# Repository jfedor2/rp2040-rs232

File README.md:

# RS-232 adapter with an RP2040 chip

This repository contains design files and firmware for a board that can be used as an RS-232 (serial) to USB adapter. It has an RP2040 chip for the application logic and a MAX3243 chip for the serial interface.

The provided firmware supports classic serial mice, two types of 3D mice (Magellan/SpaceMouse and Spaceball 2003), the SpaceOrb 360 game controller, and can also act as a generic serial-to-USB adapter.

## How to make the device

I used [JLCPCB](https://jlcpcb.com/) to make the board. The files in the [fabrication](fabrication) folder can be used with JLCPCB directly. If you want to use some other service, check the file formats that they expect. When ordering from JLCPCB, upload the Gerber zip, leave all the settings at default (you can choose the PCB color), then enable "PCB Assembly" and upload the BOM and CPL files in the next step.

Models for a 3D-printable case can be found in the [3d-printed-case](3d-printed-case) folder. The cases uses four M2x12 countersunk screws and (optionally) one M2x4 screw to secure the board to the case.

## Firmware

The provided firmware combines five separate projects and lets you choose between them using the DIP switches on the board. This way you can have a multi-purpose adapter without having to re-flash the firmware every time.

To flash the board with the firmware, press and hold the BOOT button, then while holding it press and release the RESET button. A drive named "RPI-RP2" should appear on your computer. Copy the [multi-firmware.uf2](https://github.com/jfedor2/rp2040-rs232/releases/latest/download/multi-firmware.uf2) file to that drive. After it's done flashing the drive will disappear and that's it.

project | description | DIP switch setting
------- | ----------- | ------------------
[HID Remapper](https://github.com/jfedor2/hid-remapper) | Adapts classic serial mice to USB | off-off-off-ON
[spaceball-2003](https://github.com/jfedor2/spaceball-2003) | Lets you use a Spaceball 2003 with modern software | off-off-ON-off
[magellan-spacemouse](https://github.com/jfedor2/magellan-spacemouse) | Lets you use a serial Magellan/SpaceMouse with modern software | off-off-ON-ON
[pico-uart-bridge](https://github.com/Noltari/pico-uart-bridge) | Generic USB-to-serial bridge | off-ON-off-off
[spaceorb360](https://github.com/jfedor2/spaceorb360)<br>(spacemouse) | Lets you use a SpaceOrb 360 with modern CAD software | off-ON-off-ON
[spaceorb360](https://github.com/jfedor2/spaceorb360)<br>(joystick) | Lets you use a SpaceOrb 360 with games like Descent | off-ON-ON-off

You can of course use any other firmware meant for the RP2040 chip if you want.

## How to compile

The easiest way to compile the firmware is to let GitHub do it for you. This repository has GitHub Actions that build the firmware, so you can just fork, enable Actions, make your changes, wait for the job to complete, and look for the binary in the artifacts produced.

To compile the firmware on your machine, use the following steps (details may vary depending on your Linux distribution):

```
sudo apt install gcc-arm-none-eabi libnewlib-arm-none-eabi libstdc++-arm-none-eabi-newlib
git clone https://github.com/jfedor2/rp2040-rs232.git
cd rp2040-rs232/multi-firmware
git submodule update --init
for submodule in hid-remapper magellan-spacemouse spaceball-2003 pico-uart-bridge spaceorb360
do
cd $submodule; git submodule update --init; cd ..
done
mkdir build
cd build
cmake ..
make
```

## License

The software in this repository is licensed under the [MIT License](LICENSE), unless stated otherwise. 

The hardware designs in this repository are licensed under the Creative Commons Attribution 4.0 International license ([CC BY 4.0](https://creativecommons.org/licenses/by/4.0/)), unless stated otherwise.

## Acknowledgments

PCB design uses [Type-C.pretty](https://github.com/ai03-2725/Type-C.pretty) library by [ai03-2725](https://github.com/ai03-2725).

Multi-firmware includes [pico-uart-bridge](https://github.com/Noltari/pico-uart-bridge) by [Noltari](https://github.com/Noltari).

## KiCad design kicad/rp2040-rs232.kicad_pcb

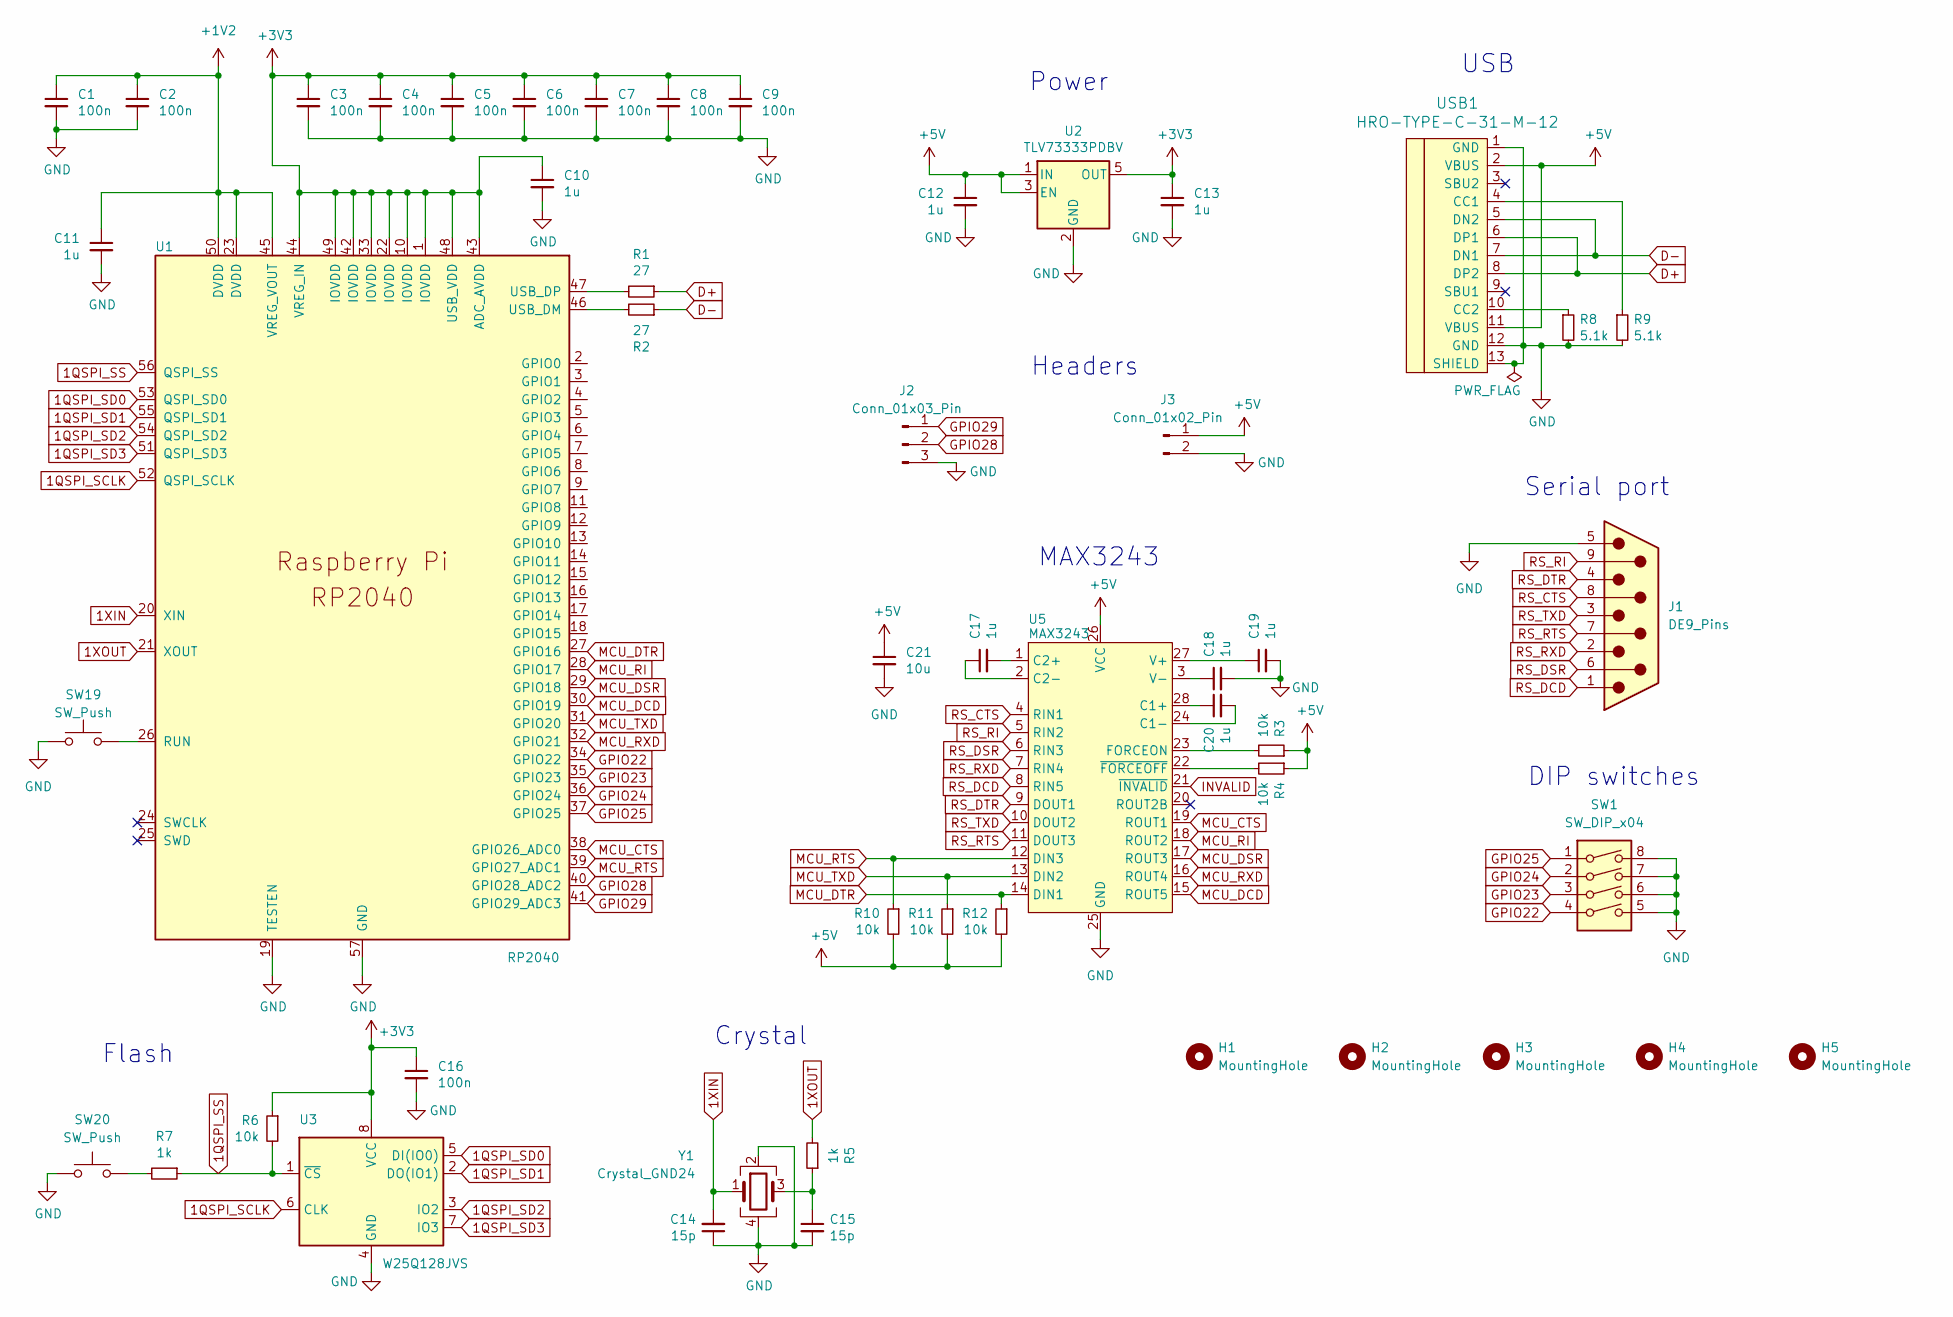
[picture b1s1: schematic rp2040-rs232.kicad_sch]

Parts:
C1, C2, C3, C4, C5, C6, C7, C8, C9, C16: 100n; C_0402_1005Metric; LCSC C1525
C10, C11, C12, C13, C17, C18, C19, C20: 1u; C_0402_1005Metric; LCSC C52923
C14, C15: 15p; C_0402_1005Metric; LCSC C1548
C21: 10u; C_0402_1005Metric; LCSC C15525
H1, H2, H3, H4, H5: MountingHole; MountingHole_2.2mm_M2
J1: DE9_Pins; C19077344; LCSC C19077344
J2: Conn_01x03_Pin; PinHeader_1x03_P2.54mm_Vertical
J3: Conn_01x02_Pin; PinHeader_1x02_P2.54mm_Vertical
R1, R2: 27; R_0402_1005Metric; LCSC C138021
R3, R4, R6, R10, R11, R12: 10k; R_0402_1005Metric; LCSC C25744
R5, R7: 1k; R_0402_1005Metric; LCSC C11702
R8, R9: 5.1k; R_0402_1005Metric; LCSC C25905
SW1: SW_DIP_x04; C92645; LCSC C92645
SW19, SW20: SW_Push; C720477; LCSC C720477
U1: RP2040; RP2040-QFN-56; LCSC C2040
U2: TLV73333PDBV; SOT-23-5; LCSC C134139
U3: W25Q128JVS; SOIC-8_5.23x5.23mm_P1.27mm; LCSC C97521
U5: MAX3243; SSOP-28_5.3x10.2mm_P0.65mm; LCSC C414614
USB1: HRO-TYPE-C-31-M-12; HRO-TYPE-C-31-M-12-Assembly; LCSC C165948
Y1: Crystal_GND24; Crystal_SMD_2520-4Pin_2.5x2.0mm; LCSC C90603

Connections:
1QSPI_SCLK: U1.52 (QSPI_SCLK), U3.6 (CLK)
1QSPI_SD0: U1.53 (QSPI_SD0), U3.5 (DI(IO0))
1QSPI_SD1: U1.55 (QSPI_SD1), U3.2 (DO(IO1))
1QSPI_SD2: U1.54 (QSPI_SD2), U3.3 (IO2)
1QSPI_SD3: U1.51 (QSPI_SD3), U3.7 (IO3)
1QSPI_SS: R6.2, R7.1, U1.56 (QSPI_SS), U3.1 (~CS)
1XIN: C14.2, U1.20 (XIN), Y1.1
1XOUT: R5.2, U1.21 (XOUT)
+1V2: C1.1, C2.1, C11.1, U1.23 (DVDD), U1.45 (VREG_VOUT), U1.50 (DVDD)
+3V3: C3.1, C4.1, C5.1, C6.1, C7.1, C8.1, C9.1, C10.1, C13.1, C16.1, R6.1, U1.1 (IOVDD), U1.10 (IOVDD), U1.22 (IOVDD), U1.33 (IOVDD), U1.42 (IOVDD), U1.43 (ADC_AVDD), U1.44 (VREG_IN), U1.48 (USB_VDD), U1.49 (IOVDD), U2.5 (OUT), U3.8 (VCC)
+5V: C12.1, C21.1, J3.1, R3.1, R4.1, R10.2, R11.2, R12.2, U2.1 (IN), U2.3 (EN), U5.26 (VCC), USB1.2 (VBUS), USB1.11 (VBUS)
D+: R1.1, USB1.6 (DP1), USB1.8 (DP2)
D-: R2.1, USB1.5 (DN2), USB1.7 (DN1)
GND: C1.2, C2.2, C3.2, C4.2, C5.2, C6.2, C7.2, C8.2, C9.2, C10.2, C11.2, C12.2, C13.2, C14.1, C15.2, C16.2, C18.2, C19.2, C21.2, J1.5, J2.3, J3.2, R8.2, R9.2, SW1.5, SW1.6, SW1.7, SW1.8, SW19.1, SW20.1, U1.19 (TESTEN), U1.57 (GND), U2.2 (GND), U3.4 (GND), U5.25 (GND), USB1.1 (GND), USB1.12 (GND), USB1.13 (SHIELD), Y1.2, Y1.4
GPIO22: SW1.4, U1.34 (GPIO22)
GPIO23: SW1.3, U1.35 (GPIO23)
GPIO24: SW1.2, U1.36 (GPIO24)
GPIO25: SW1.1, U1.37 (GPIO25)
GPIO28: J2.2, U1.40 (GPIO28_ADC2)
GPIO29: J2.1, U1.41 (GPIO29_ADC3)
INVALID: U5.21 (~INVALID)
MCU_CTS: U1.38 (GPIO26_ADC0), U5.19 (ROUT1)
MCU_DCD: U1.30 (GPIO19), U5.15 (ROUT5)
MCU_DSR: U1.29 (GPIO18), U5.17 (ROUT3)
MCU_DTR: R12.1, U1.27 (GPIO16), U5.14 (DIN1)
MCU_RI: U1.28 (GPIO17), U5.18 (ROUT2)
MCU_RTS: R10.1, U1.39 (GPIO27_ADC1), U5.12 (DIN3)
MCU_RXD: U1.32 (GPIO21), U5.16 (ROUT4)
MCU_TXD: R11.1, U1.31 (GPIO20), U5.13 (DIN2)
unnamed: C15.1, R5.1, Y1.3
unnamed: R7.2, SW20.2
unnamed: SW19.2, U1.26 (RUN)
unnamed: R2.2, U1.46 (USB_DM)
unnamed: R1.2, U1.47 (USB_DP)
unnamed: C20.1, U5.28 (C1+)
unnamed: C20.2, U5.24 (C1-)
unnamed: C17.2, U5.1 (C2+)
unnamed: C17.1, U5.2 (C2-)
unnamed: R3.2, U5.23 (FORCEON)
unnamed: C19.1, U5.27 (V+)
unnamed: C18.1, U5.3 (V-)
unnamed: R4.2, U5.22 (~FORCEOFF)
unnamed: R9.1, USB1.4 (CC1)
unnamed: R8.1, USB1.10 (CC2)
RS_CTS: J1.8, U5.4 (RIN1)
RS_DCD: J1.1, U5.8 (RIN5)
RS_DSR: J1.6, U5.6 (RIN3)
RS_DTR: J1.4, U5.9 (DOUT1)
RS_RI: J1.9, U5.5 (RIN2)
RS_RTS: J1.7, U5.11 (DOUT3)
RS_RXD: J1.2, U5.7 (RIN4)
RS_TXD: J1.3, U5.10 (DOUT2)

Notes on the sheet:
Crystal
Headers
MAX3243
Serial port
DIP switches
Power
Flash
USB

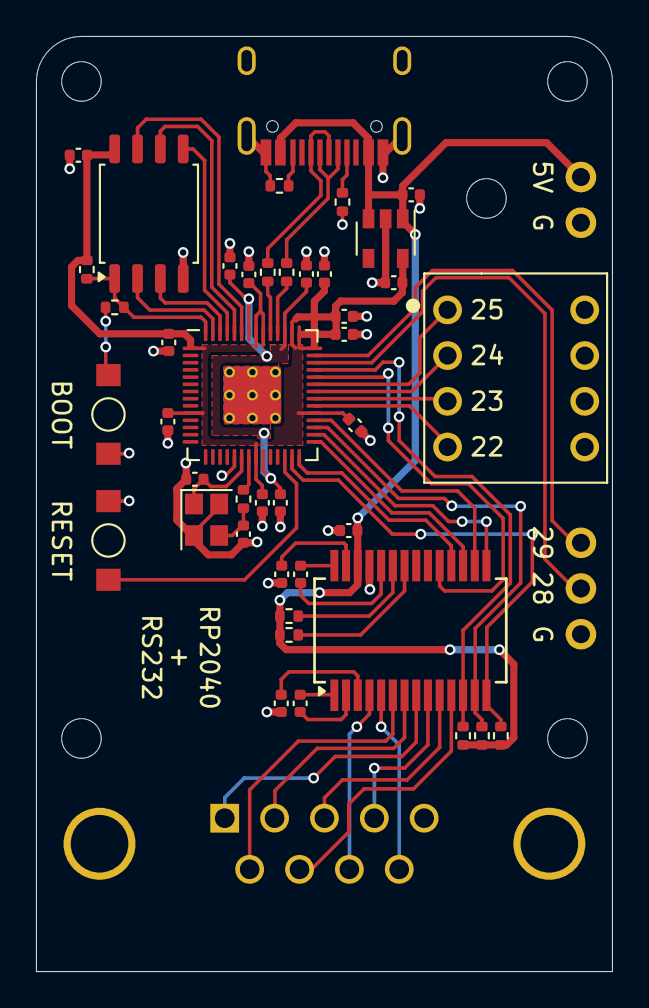
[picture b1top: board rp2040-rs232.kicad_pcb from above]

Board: 2 copper layers, 32.0 x 52.0 mm, 50 parts (0 on the bottom side), 51 nets.

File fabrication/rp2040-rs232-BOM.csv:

"Value","Reference","Footprint","LCSC"
"100n","C1,C2,C3,C4,C5,C6,C7,C8,C9,C16","Capacitor_SMD:C_0402_1005Metric","C1525"
"1u","C10,C11,C12,C13,C17,C18,C19,C20","Capacitor_SMD:C_0402_1005Metric","C52923"
"15p","C14,C15","Capacitor_SMD:C_0402_1005Metric","C1548"
"10u","C21","Capacitor_SMD:C_0402_1005Metric","C15525"
"DE9_Pins","J1","DE-9:C19077344","C19077344"
"27","R1,R2","Resistor_SMD:R_0402_1005Metric","C138021"
"10k","R3,R4,R6,R10,R11,R12","Resistor_SMD:R_0402_1005Metric","C25744"
"1k","R5,R7","Resistor_SMD:R_0402_1005Metric","C11702"
"5.1k","R8,R9","Resistor_SMD:R_0402_1005Metric","C25905"
"SW_DIP_x04","SW1","DIP:C92645","C92645"
"SW_Push","SW19,SW20","SW:C720477","C720477"
"RP2040","U1","RP2040:RP2040-QFN-56","C2040"
"TLV73333PDBV","U2","SOT-23-5:SOT-23-5","C134139"
"W25Q128JVS","U3","SOIC:SOIC-8_5.23x5.23mm_P1.27mm","C97521"
"MAX3243","U5","MAX3243:SSOP-28_5.3x10.2mm_P0.65mm","C414614"
"HRO-TYPE-C-31-M-12","USB1","Type-C:HRO-TYPE-C-31-M-12-Assembly","C165948"
"Crystal_GND24","Y1","Crystal:Crystal_SMD_2520-4Pin_2.5x2.0mm","C90603"

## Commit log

2026-02-24 Add .bin files to BYPRODUCTS and DEPENDS
    Without this the combined UF2 wasn't rebuilt when one of the
    subprojects was updated.
2026-02-24 Change "OFF" to "off" in README
2026-02-24 Add SpaceOrb 360 firmware
2026-02-25 Update building instructions
